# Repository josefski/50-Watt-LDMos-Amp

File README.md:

# 50-Watt-LDMos-Amp
Inspiration for this project came from here: https://ludens.cl/Electron/50Wamp/50Wamp.html 

A 50 Watt HF Amp that uses modern parts 

This is mostly clanker code for a raspberry pi pico controlled protection loop and operation control for a 50 watt HF Amplifier that uses modern LDmos transistors instead of the IRF series mosfets that are 50 years old and inappropriate for this purpose. 

This is ultimately intended for use as a portable amplifier aimed at SOTA and to a lesser extent POTA operators who want to add some power to their QMX or other QRP radios. The majority of designs available on the internet are built around the IRF 510 or IRF 530 mosfet, and while it's impressive that an hf amp can be built around those parts, they're not very well suited to the purpose. This is designed around the AFT05MP Dual LDmos from NXP, which is currently not recommended for new designs. It's a dual ldmos rf amplifier designed to work up to 530 Mhz. Another rf power transistor that could be substituted would be the BLP5LA55 series LDMOS from Ampleon, which are newer but don't come in the handy dual package. There aren't a lot of 12-15 volt RF mosfets on the market. We're a small niche.  

Principle design goals are as follows: 

-12 volt operation
-Uses actual RF power transistors, preferably ldmos
-No unobtainium parts
-Currently manufactured components only
-Keep parts reasonably affordable
-Smaller heatsink with shortened fins and permanently mounted cooling fans for improved portability 
-Ruggedized, completed design, meaning full protections from drain overvoltage, overcurrent, oscillation, and overtemperature
-Able to be used in line with an antenna tuner!!!!!!!! (Seriously. A portable amp is next to useless without that capability. Finish the design job.) 
-40-10meter operation. Requires only three filter banks. Don't care about the other bands. This is for portable use. 50 watts won't get you over the noise floor on 80 meters anyway.  
-A real Keyer input. No RF sense keying. It's annoying to use. 
-Manual band switching. 
-Always <2:1 input SWR. The amp should never under any circumstance cause the QMX to shut off. 
-Amp shuts off in response to excess current and drain voltage excursions, not high SWR. High SWR doesn't kill transistors. High drain voltage and overcurrent does. 
-Display all relevant parameters and return comprehensible error codes 
-Maybe full QSK. We'll see. Would be nice but not a specific deal breaker. 
-Maybe Variable input attenuation to compensate for QMX low output on 17 and 21 meters. Cool idea but requires some deep thought.

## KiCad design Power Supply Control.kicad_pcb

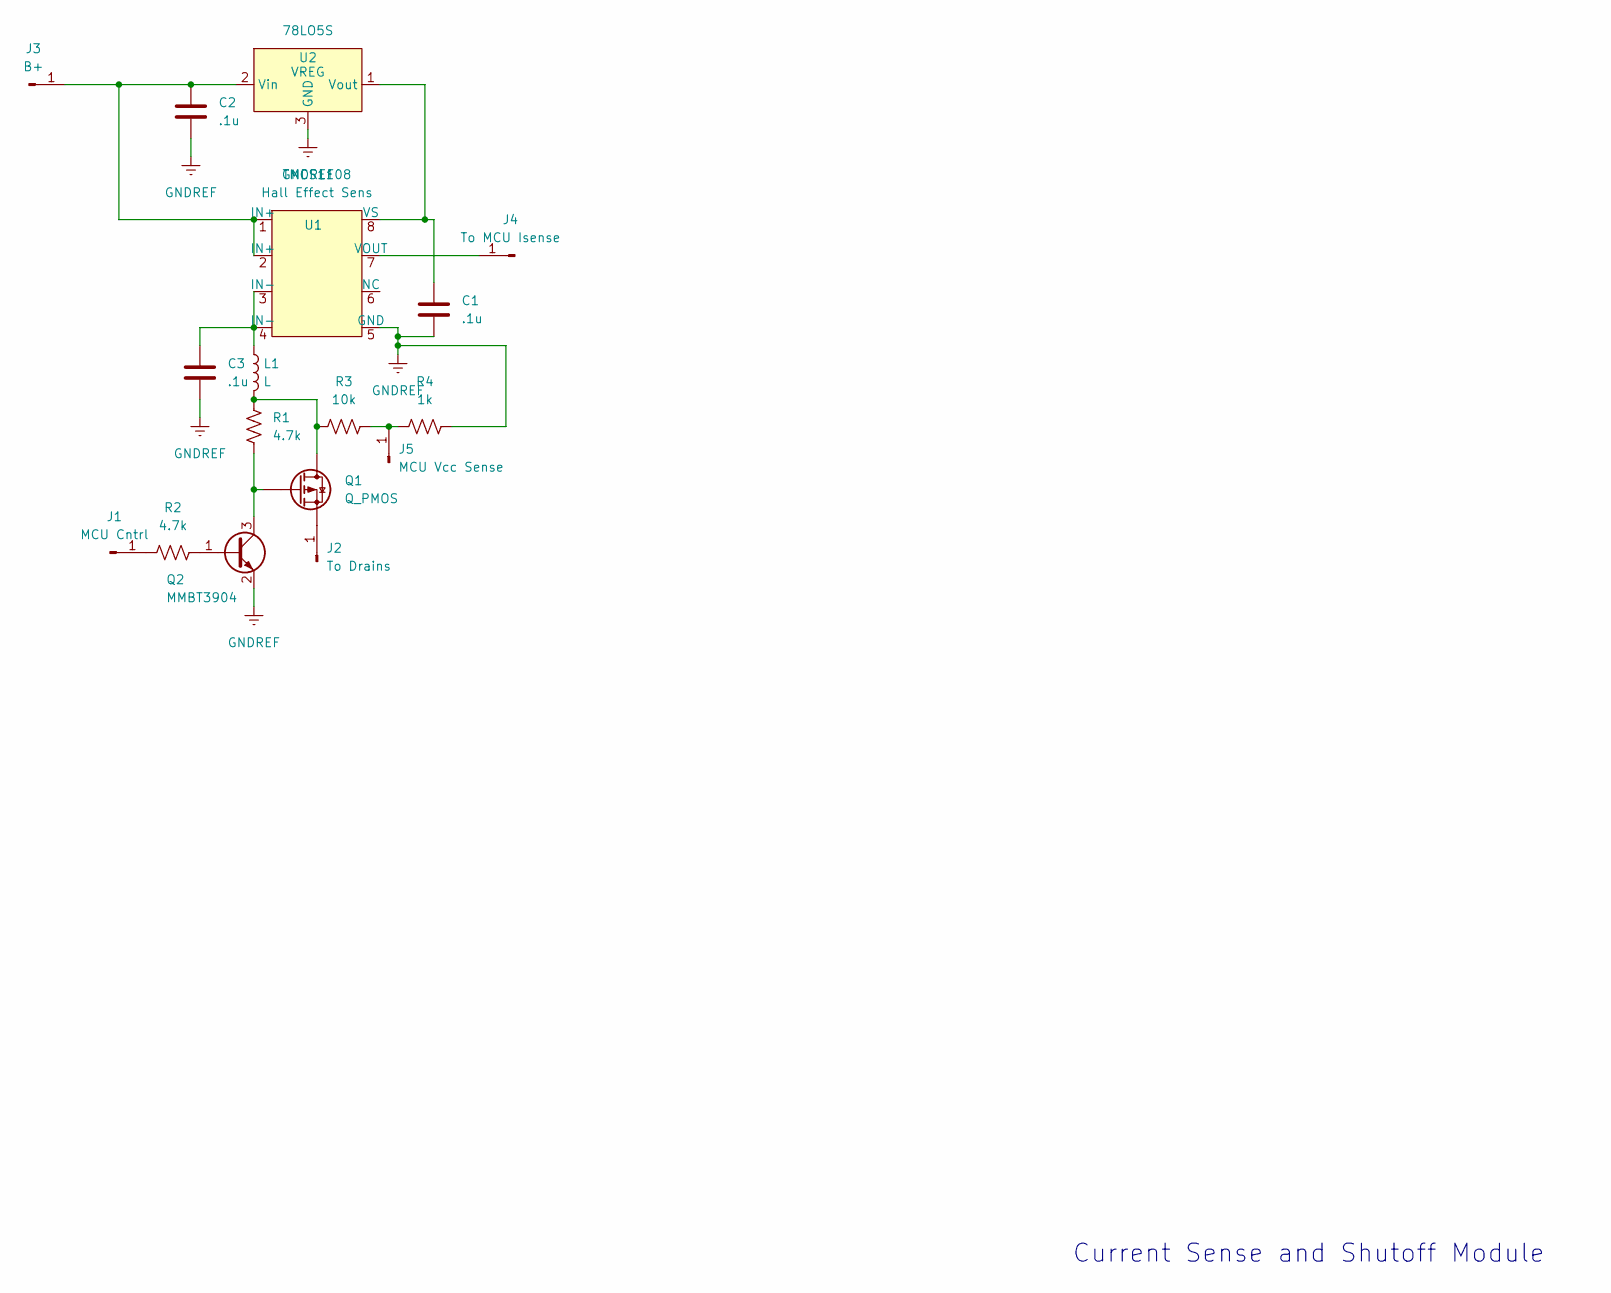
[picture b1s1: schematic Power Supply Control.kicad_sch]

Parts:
C1, C2: .1u; C_0805_2012Metric_Pad1.18x1.45mm_HandSolder
C3: .1u; .33uF Decoupler HF Amp
J1: MCU Cntrl; Single Surface Mount Header
J2: To Drains; Single Surface Mount Header
J3: B+; Single Surface Mount Header
J4: To MCU Isense; Single Surface Mount Header
J5: MCU Vcc Sense; Single Surface Mount Header
L1: L; Input Choke
Q1: Q_PMOS; Josef TO-252-2
Q2: MMBT3904; SOT-23
R1, R2: 4.7k; R_0805_2012Metric_Pad1.20x1.40mm_HandSolder
R3: 10k; R_0805_2012Metric_Pad1.20x1.40mm_HandSolder
R4: 1k; R_0805_2012Metric_Pad1.20x1.40mm_HandSolder
U1: TMCS1108; SOIC-8 Hall Effect Footprint
U2: 78LO5S; SOT-23

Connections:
GNDREF: C1.2, C2.2, C3.2, Q2.2 (E), R4.2, U1.5 (GND), U2.3 (GND)
unnamed: C3.1, L1.1, U1.3 (IN-), U1.4 (IN-)
unnamed: J1.1, R2.1
unnamed: J2.1, Q1.1 (S)
unnamed: C2.1, J3.1, U1.1 (IN+), U1.2 (IN+), U2.2 (Vin)
unnamed: J4.1, U1.7 (VOUT)
unnamed: J5.1, R3.2, R4.1
unnamed: L1.2, Q1.3 (D), R1.1, R3.1
unnamed: Q1.2 (G), Q2.3 (C), R1.2
unnamed: Q2.1 (B), R2.2
unnamed: C1.1, U1.8 (VS), U2.1 (Vout)

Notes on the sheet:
Current Sense and Shutoff Module

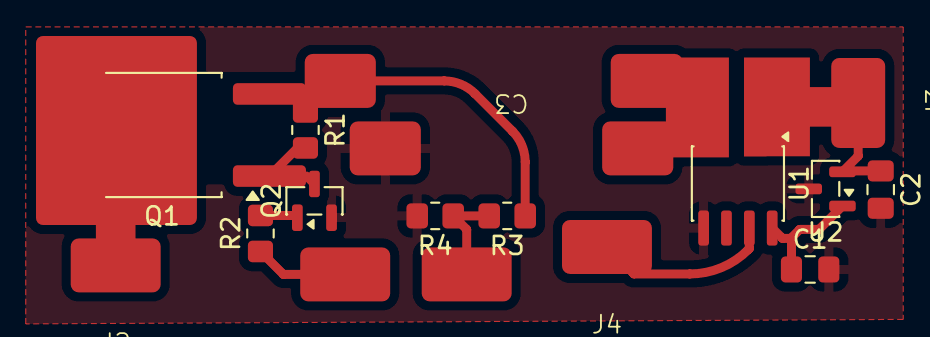
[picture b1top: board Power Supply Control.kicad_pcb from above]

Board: 2 copper layers, 17 parts (0 on the bottom side), 11 nets.

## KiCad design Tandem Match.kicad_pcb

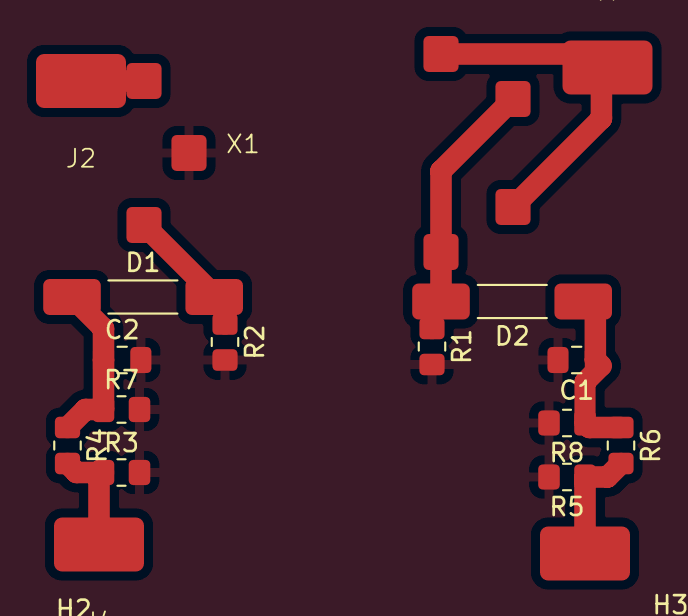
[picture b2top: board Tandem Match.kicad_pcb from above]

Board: 2 copper layers, 21 parts (0 on the bottom side), 9 nets.

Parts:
C1, C2: .1u; C_0805_2012Metric_Pad1.18x1.45mm_HandSolder
D1, D2: D; Through Hole Resistor
H1, H2, H3, H4: MountingHole_Pad; MountingHole_3.2mm_M3
J1, J2, J3, J4: Conn_01x01_Pin; Single Surface Mount Header
R1, R2: 50; R_0805_2012Metric_Pad1.20x1.40mm_HandSolder
R3, R5, R7, R8: 10k; R_0805_2012Metric_Pad1.20x1.40mm_HandSolder
R4, R6: 33k; R_0805_2012Metric_Pad1.20x1.40mm_HandSolder
X1: Tandem Match

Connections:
GNDREF: C1.2, C2.2, R1.2, R2.2, R3.2, R5.2, R7.2, R8.2, X1.3 (S)
unnamed: D1.2 (A), R2.1, X1.2
unnamed: C2.1, D1.1 (K), R4.1, R7.1
unnamed: D2.2 (A), R1.1, X1.4, X1.6 (P2_Out)
unnamed: C1.1, D2.1 (K), R6.1, R8.1
unnamed: J1.1, X1.5, X1.7 (P1_Out)
unnamed: J2.1, X1.1
unnamed: J3.1, R5.1, R6.2
unnamed: J4.1, R3.1, R4.2

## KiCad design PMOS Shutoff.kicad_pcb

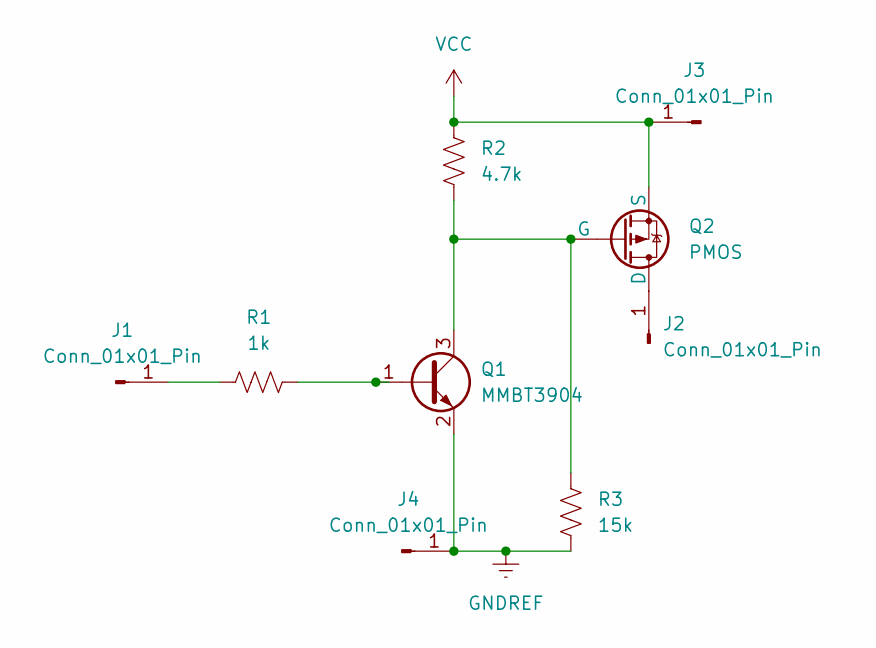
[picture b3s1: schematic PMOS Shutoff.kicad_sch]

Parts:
J1, J2, J3, J4: Conn_01x01_Pin; Single Surface Mount Header
Q1: MMBT3904; SOT-23
Q2: PMOS; Josef TO-252-2
R1: 1k; R_0805_2012Metric_Pad1.20x1.40mm_HandSolder
R2: 4.7k; R_0805_2012Metric_Pad1.20x1.40mm_HandSolder
R3: 15k; R_0805_2012Metric_Pad1.20x1.40mm_HandSolder

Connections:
GNDREF: J4.1, Q1.2 (E), R3.1
unnamed: J1.1, R1.1
unnamed: J2.1, Q2.1 (D)
unnamed: Q1.1 (B), R1.2
unnamed: Q1.3 (C), Q2.2 (G), R2.1, R3.2
VCC: J3.1, Q2.3 (S), R2.2

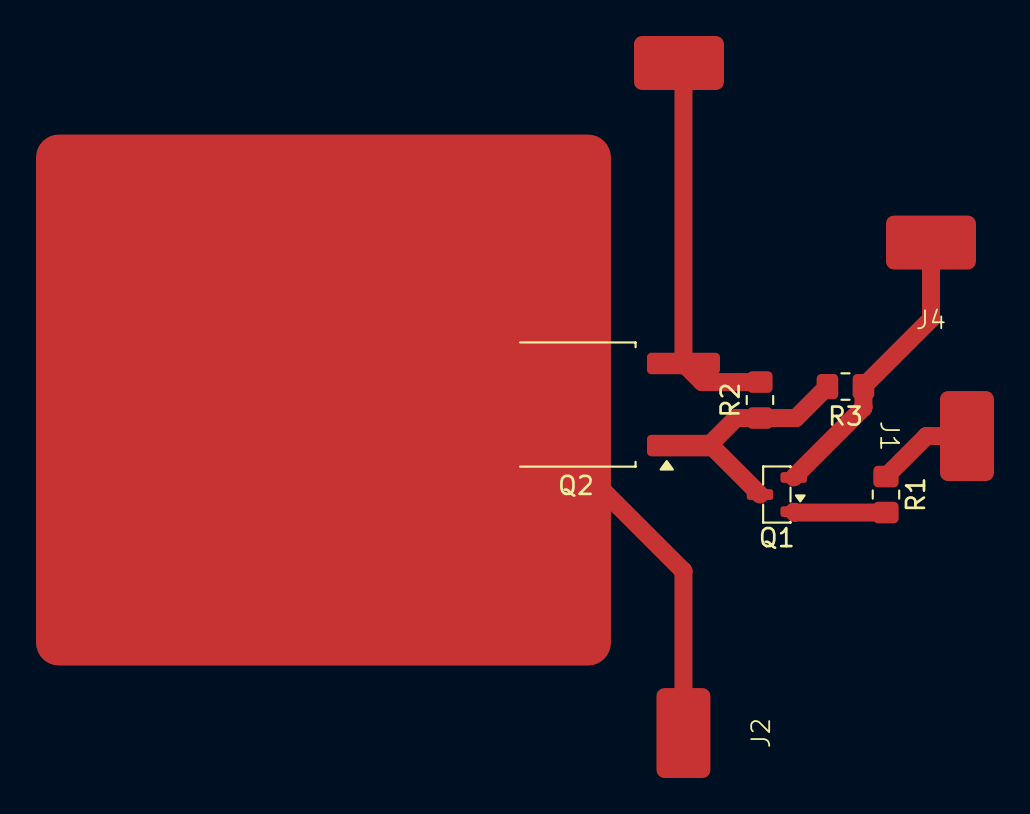
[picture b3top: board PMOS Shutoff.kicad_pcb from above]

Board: 2 copper layers, 9 parts (0 on the bottom side), 6 nets.

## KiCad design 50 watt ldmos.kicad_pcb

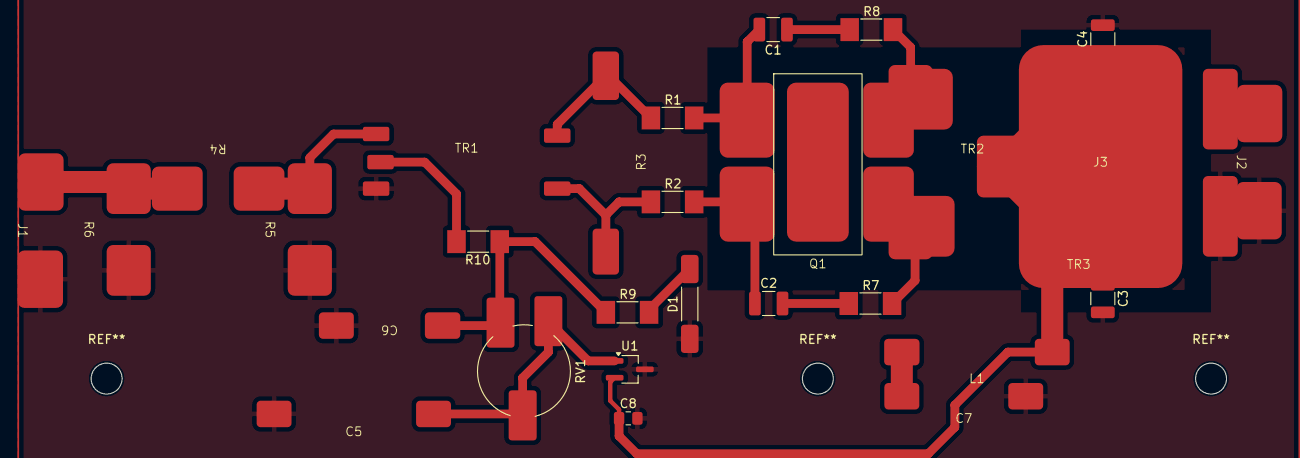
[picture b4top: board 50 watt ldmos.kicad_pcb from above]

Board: 2 copper layers, 29 parts (0 on the bottom side), 18 nets.

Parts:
C1, C2, C3, C4: .1uF; C_1210_3225Metric_Pad1.33x2.70mm_HandSolder
C5: 15u; 10uF Radial Cap
C6: 220u; 220 uf Cap
C7: .1uF; .33uF Decoupler HF Amp
C8: .1u; C_0805_2012Metric_Pad1.18x1.45mm_HandSolder
D1: D; Through Hole Resistor
J1, J2: Conn_01x02_Pin; InOutNoHeaders
J3: Conn_01x01_Pin; Positive Plane
L1: L; Input Choke
Q1: AFT05MP
R1, R2, R10: 10; R_MELF_MMB-0207
R3: 22; Big 22ohm Resistor
R4, R5, R6: R; 3550 (Big Resistor) Footprint
R7, R8, R9: 220; R_MELF_MMB-0207
RV1: R_Potentiometer; Piher Surface Pads
TR1: 2T - 1T; Input Transformer
TR2: TRANSF1; Coaxial Feed Transformer
TR3: 1T 3T; Output Transformer
U1: L78L05_TO92; TSOT-23_HandSoldering

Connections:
+12V: C7.1, L1.1
GNDREF: C3.2, C4.2, C5.2, C6.2, C7.2, C8.2, D1.1 (K), J1.2, J2.2, Q1.5 (Source), R5.1, R6.1, TR1.2, TR3.3, U1.3 (GND)
unnamed: C1.1, R8.1
unnamed: C2.2, R7.1
unnamed: C6.1, R9.1, R10.1, RV1.1
unnamed: D1.2 (A), R9.2
unnamed: J1.1, R4.1, R6.2
unnamed: J2.1, TR3.4
unnamed: Q1.3 (D1), R8.2, TR2.1, TR3.1
unnamed: Q1.4 (D2), R7.2, TR2.3 (S3), TR3.2
unnamed: C1.2, Q1.1 (G1), R1.2
unnamed: C2.1, Q1.2 (G2), R2.2
unnamed: R1.1, R3.2, TR1.4
unnamed: R2.1, R3.1, TR1.5
unnamed: R4.2, R5.2, TR1.1
unnamed: R10.2, TR1.3
unnamed: C3.1, C4.1, C8.1, L1.2, TR2.2, TR2.4 (S4), U1.2 (VI)
unnamed: C5.1, RV1.2, RV1.3, U1.1 (VO)

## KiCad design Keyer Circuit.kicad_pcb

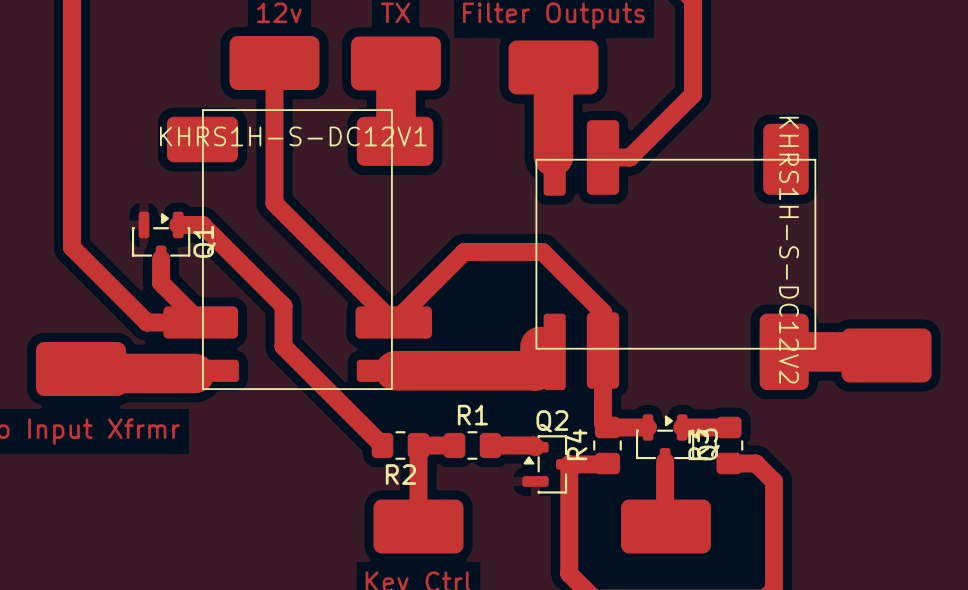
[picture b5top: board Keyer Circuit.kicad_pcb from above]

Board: 2 copper layers, 16 parts (0 on the bottom side), 14 nets.

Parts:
J1: To Bias +; Single Surface Mount Header
J2: To Input Xfrmr; Single Surface Mount Header
J3: Key Ctrl; Single Surface Mount Header
J4: Filter Outputs; Single Surface Mount Header
J7: Antenna; Single Surface Mount Header
J8: TX; Single Surface Mount Header
J9: 12v; Single Surface Mount Header
KHRS1H-S-DC12V1, KHRS1H-S-DC12V2: HRS1H Relay No Hole
Q1, Q2: MMBT3904; SOT-23
Q3: MMBT3906; SOT-23
R1, R2, R3, R4: 4.7k; R_0805_2012Metric_Pad1.20x1.40mm_HandSolder

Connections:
GNDREF: Q1.2 (E), Q2.2 (E)
unnamed: J1.1, Q3.3 (C)
unnamed: J2.1, KHRS1H-S-DC12V1.NO
unnamed: J3.1, R1.1, R2.1
unnamed: J4.1, KHRS1H-S-DC12V2.NO
unnamed: J7.1, KHRS1H-S-DC12V2.COM2
unnamed: J8.1, KHRS1H-S-DC12V1.COM2
unnamed: KHRS1H-S-DC12V1.NC, KHRS1H-S-DC12V2.NC
unnamed: Q1.1 (B), R2.2
unnamed: KHRS1H-S-DC12V1.A1, KHRS1H-S-DC12V2.A1, Q1.3 (C)
unnamed: Q2.1 (B), R1.2
unnamed: Q2.3 (C), R3.1, R4.1
unnamed: Q3.1 (B), R3.2
VCC: J9.1, KHRS1H-S-DC12V1.A2, KHRS1H-S-DC12V2.A2, Q3.2 (E), R4.2

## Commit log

2026-01-19 Enhance README with project details
    Added a detailed explanation about the amplifier's control loop and components.
2026-01-19 Add swr_table.csv detector calibration
2026-01-19 Expand README with project inspiration and design goals
    Added project inspiration and detailed design goals for the 50 Watt LDMos Amplifier.
2026-01-29 Add reconstructed a2d.py ADS1115 wrapper and constants
2026-02-04 Refactor display for 16x2 I2C LCD; update main to publish band index to display state
2026-02-08 Initial plan
2026-02-08 Display: switch to 16x2 layout; publish band index; add keyer skeleton
2026-02-08 Update LCD renderer for 16x2 I2C display
2026-02-08 Refactor comments and include band index in state
    Updated comments for clarity and added band index to state.
2026-02-21 PDF, pcb, and sch files for various modules.
    The schematic files should look familiar. The PCB's may look strange as they're intended to not require any drilling. All through hole component are treated as surface mount. Bend the leads and solde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
2026-03-05 Add ATU-100 tuning mode with switchable input attenuator
    Implements a tuning mode state machine that inserts an attenuator on the
    amp input, triggers a tuning cycle on the integrated ATU-100, waits for
    completion (via busy signal or timeout), then removes the attenuator.
    New module tune_mode.py (TuneMode class):
    - 5-state machine: IDLE -> ATT_IN -> TRIGGER -> WAITING -> ATT_OUT -> IDLE
    - Dedicated button (GP8) starts sequence only when amp is enabled and healthy
2026-03-05 Revert "Add ATU-100 tuning mode with switchable input attenuator"
    This reverts commit 91d47519f2229c1e908ea2e09ab52de9c08fcdd6.
2026-03-06 Optimize and clean up across modules
    - control.py: remove unreachable thermal dead-code block after return in
    _fault_reason(); switch telemetry dict access from .get() to direct []
    in both _fault_reason() and update() for hot-path speed
    - v_drain.py, Vcc.py, current_sense.py: collapse per-read ADC arithmetic
    into a single precomputed constant (_K) at __init__; each read is now
    one multiply instead of two divides + a multiply
2026-03-07 Recalibrate drain voltage scale factor
    Was reading 12.7V at an actual 13.4V supply.
    New scale = 16.6666 * (13.4 / 12.7) = 17.5853.
    https://claude.ai/code/session_017ST951dEHBYPp529hkpVfW
2026-03-07 Fix display blank: replace bisect with inline binary search in interp.py
    bisect.bisect_right() can crash at runtime on some MicroPython builds
    when passed a regular Python list, even though the module imports fine.
    The t_swr block fires 10 ms into the main loop -- well before the first
    250 ms LCD update -- so the crash leaves the display permanently blank
    after the startup splash.
    Replace with a pure-Python binary search that is guaranteed to work on
2026-03-07 Fix KeyError: id in display LINE1 format string
    MicroPython's str.format() conflicts with 'id' as a named placeholder
    because id() is a Python built-in. Rename the key from {id} to {ia}
    (drain current in amps) in both the template and the format() call.
    https://claude.ai/code/session_017ST951dEHBYPp529hkpVfW
2026-03-07 Adopt user's preferred display.py; fix band label truncation
    - display.py: use user's preferred version as base; fix format call
    from id= to ia= to match the {ia} placeholder in display_config.py
    - display_config.py: shorten LINE0 from 19 to exactly 16 chars by
    removing the " B:" prefix before the band label, so the band is
    always visible: "S:{swr} P:{pfwd}W{band}" fills to exactly 16
    Example output:
2026-03-07 Simplify display: remove _fmt_swr, use 2-char integer fields throughout
    - Drop _fmt_swr function; inline SWR as 2-char integer in update()
    Shows "--" when no RF, integer SWR (e.g. "3") when transmitting
    - All fields now width=2: swr, pfwd, ia, vd
    - Update display_config.py comments to match
    Example output:
    Row 0: "S:-- P: 0W40 " (idle)
